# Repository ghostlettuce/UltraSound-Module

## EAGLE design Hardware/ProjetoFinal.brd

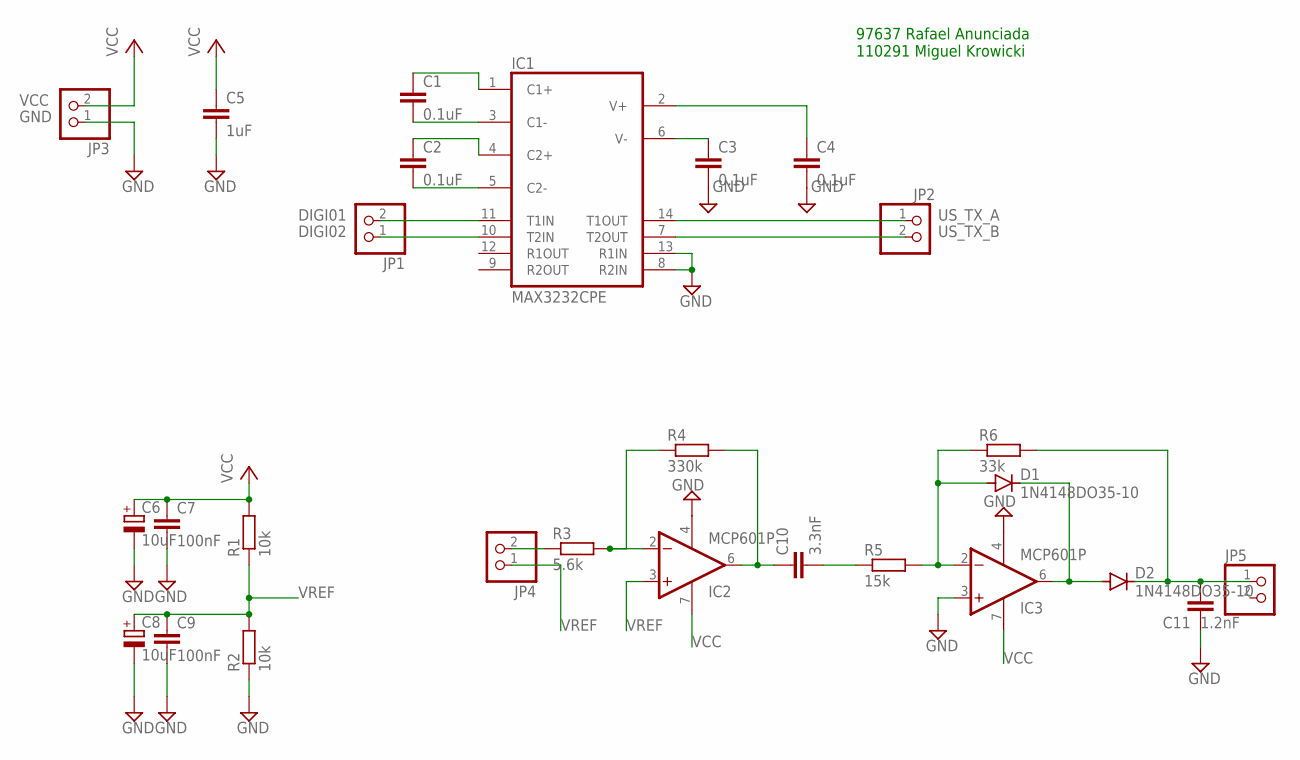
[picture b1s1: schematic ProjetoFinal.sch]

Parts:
C1, C2, C3, C4: 0.1uF; C025-025X050
C5: 1uF; C025-025X050
C6, C8: 10uF; E2,5-6
C7, C9: 100nF; C025-025X050
C10: 3.3nF; C025-025X050
C11: 1.2nF; C025-025X050
D1, D2: 1N4148DO35-10; DO35-10
IC1: MAX3232CPE; DIL16
IC2, IC3: MCP601P; DIL08
JP1, JP2, JP3, JP4, JP5: PINHD-1X2; 1X02
R1, R2: 10k; 0207/10
R3: 5.6k; 0207/10
R4: 330k; 0207/10
R5: 15k; 0207/10
R6: 33k; 0207/10

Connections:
DIGI01: IC1.11 (T1IN), JP1.2
DIGI02: IC1.10 (T2IN), JP1.1
GND: C3.2, C4.2, C5.2, C6.-, C7.2, C8.-, C9.2, C11.1, IC1.8 (R2IN), IC1.13 (R1IN), IC1.15 (GND), IC2.4 (V-), IC3.3 (+IN), IC3.4 (V-), JP3.1, R2.1
unnamed: C1.2, IC1.3 (C1-)
unnamed: C1.1, IC1.1 (C1+)
unnamed: C2.2, IC1.5 (C2-)
unnamed: C2.1, IC1.4 (C2+)
unnamed: C3.1, IC1.6 (V-)
unnamed: C4.1, IC1.2 (V+)
unnamed: JP4.2, R3.1
unnamed: C10.1, IC2.6 (OUT), R4.2
unnamed: C10.2, R5.1
unnamed: D1.A, IC3.2 (-IN), R5.2, R6.1
unnamed: D1.C, D2.A, IC3.6 (OUT)
unnamed: C11.2, D2.C, JP5.1, R6.2
unnamed: IC2.2 (-IN), R3.2, R4.1
US_TX_A: IC1.14 (T1OUT), JP2.1
US_TX_B: IC1.7 (T2OUT), JP2.2
VCC: C5.1, C6.+, C7.1, IC1.16 (VCC), IC2.7 (V+), IC3.7 (V+), JP3.2, R1.2
VREF: C8.+, C9.1, IC2.3 (+IN), JP4.1, R1.1, R2.2

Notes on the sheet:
97637 Rafael Anunciada 110291 Miguel Krowicki

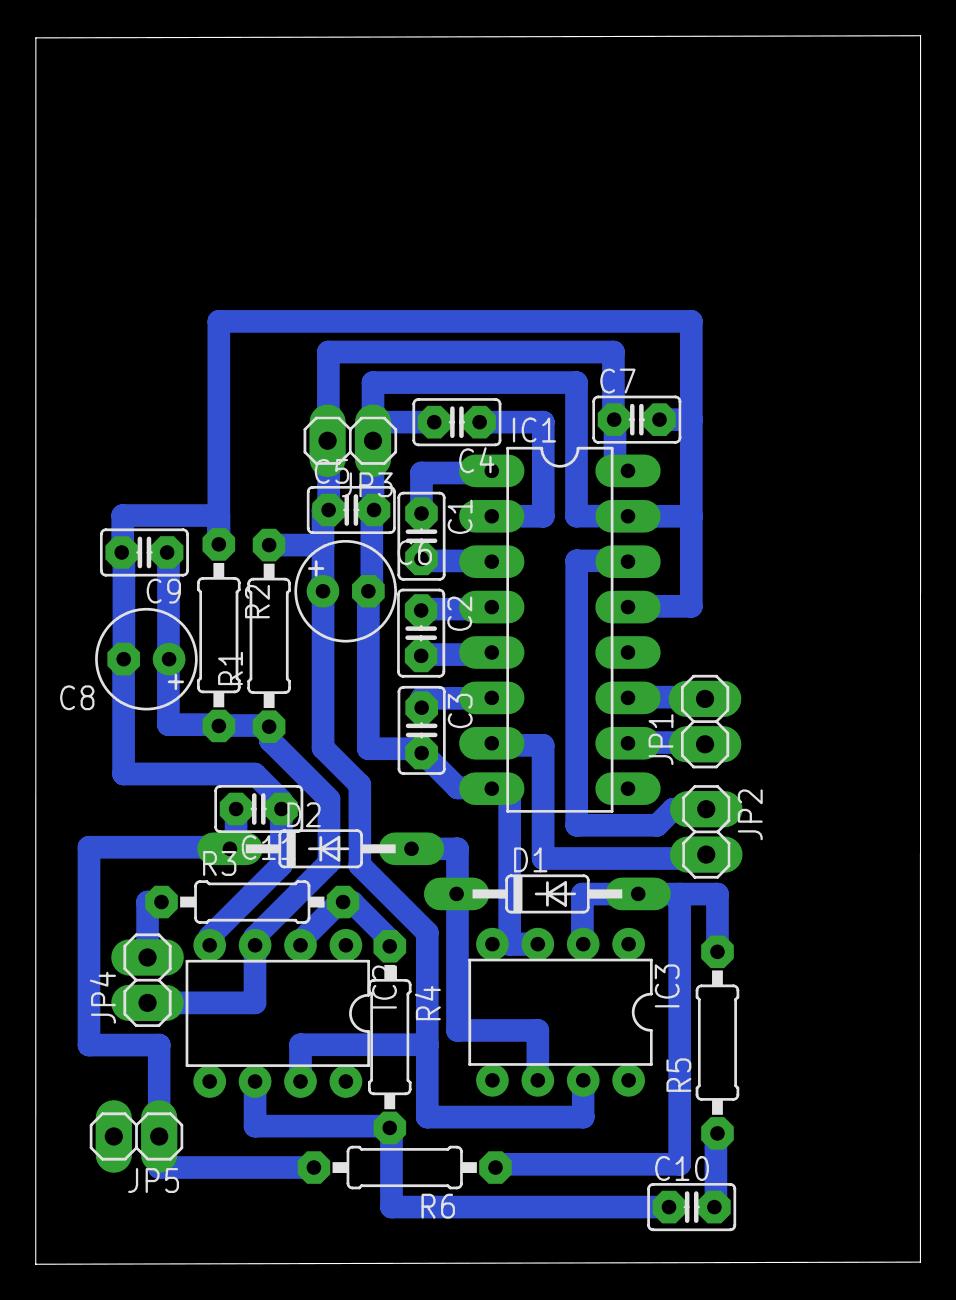
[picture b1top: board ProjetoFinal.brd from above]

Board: 2 copper layers, 49.5 x 68.7 mm, 27 parts (0 on the bottom side), 20 nets.

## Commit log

2022-06-05 Hardware update
2022-06-06 Base software added
